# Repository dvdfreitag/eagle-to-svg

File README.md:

# eagle-to-svg    

Generates an svg image from eagle schematic and board files

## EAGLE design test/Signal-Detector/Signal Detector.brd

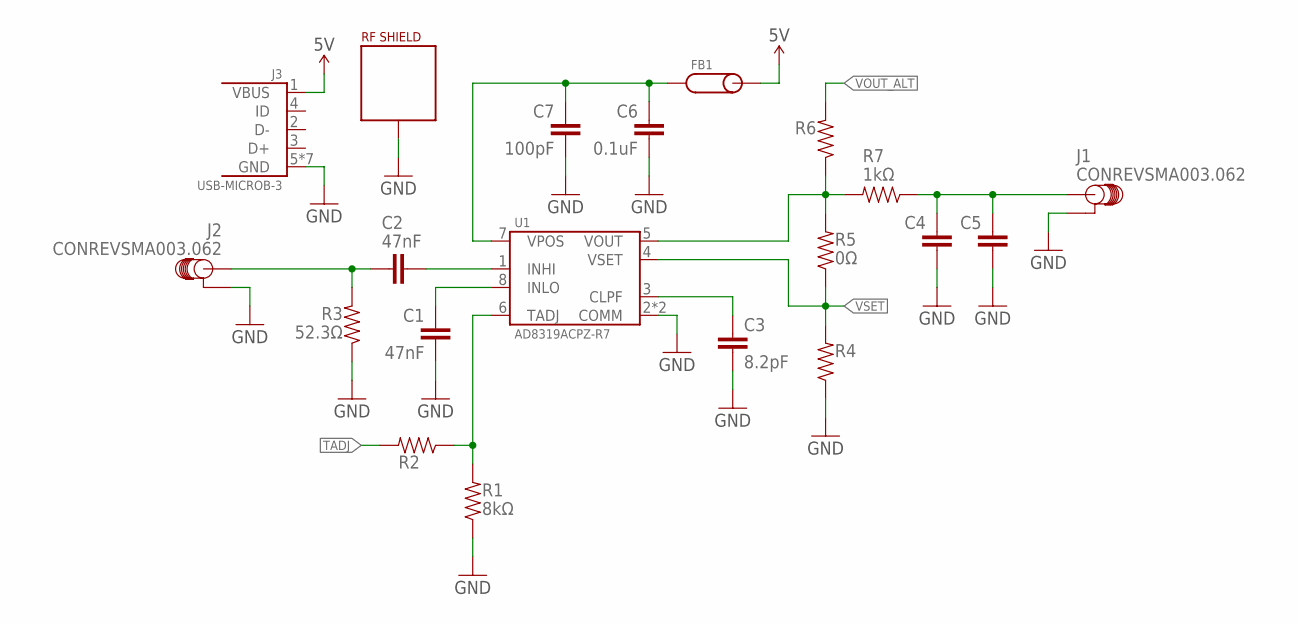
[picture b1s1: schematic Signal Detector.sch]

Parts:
C1, C2: 47nF; 0603-CAP
C3: 8.2pF; 0603-CAP
C4, C5: CAP-0603; 0603-CAP
C6: 0.1uF; 0603-CAP
C7: 100pF; 0603-CAP
FB1: FERRITE-0603; 0603-FERRITE
J1, J2: CONREVSMA003.062; SMA-EDGE
J3: USB-MICROB-3; 10118192-0001LF
R1: 8kΩ; 0603-CAP
R2, R4, R6: RESISTOR-0603; 0603-CAP
R3: 52.3Ω; 0603-CAP
R5: 0Ω; 0603-CAP
R7: 1kΩ; 0603-CAP
U1: AD8319ACPZ-R7; VFDFN-8-3X2
U$1: RF-SHIELD; RF_SHIELD-.65X.65

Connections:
5V: FB1.P$2, J3.1 (VBUS)
GND: C1.2, C3.2, C4.2, C5.2, C6.2, C7.2, J1.P$1 (GND), J1.P$2 (GND), J1.P$3 (GND), J1.P$4 (GND), J2.P$1 (GND), J2.P$2 (GND), J2.P$3 (GND), J2.P$4 (GND), J3.5 (GND), J3.P$6 (GND), J3.P$7 (GND), J3.P$8 (GND), J3.P$9 (GND), J3.P$10 (GND), J3.P$11 (GND), R1.1, R3.1, R4.1, U1.2 (COMM), U1.PAD (COMM), U$1.P$1, U$1.P$2, U$1.P$3, U$1.P$4, U$1.P$5, U$1.P$6, U$1.P$7, U$1.P$8, U$1.P$9, U$1.P$10, U$1.P$11, U$1.P$12
unnamed: R1.2, R2.1, U1.6 (TADJ)
unnamed: C1.1, U1.8 (INLO)
unnamed: C2.2, J2.SIGNAL, R3.2
unnamed: C2.1, U1.1 (INHI)
unnamed: C3.1, U1.3 (CLPF)
unnamed: R5.2, R6.1, R7.2, U1.5 (VOUT)
unnamed: C4.1, C5.1, J1.SIGNAL, R7.1
unnamed: C6.1, C7.1, FB1.P$1, U1.7 (VPOS)
TADJ: R2.2
VOUT_ALT: R6.2
VSET: R4.2, R5.1, U1.4 (VSET)

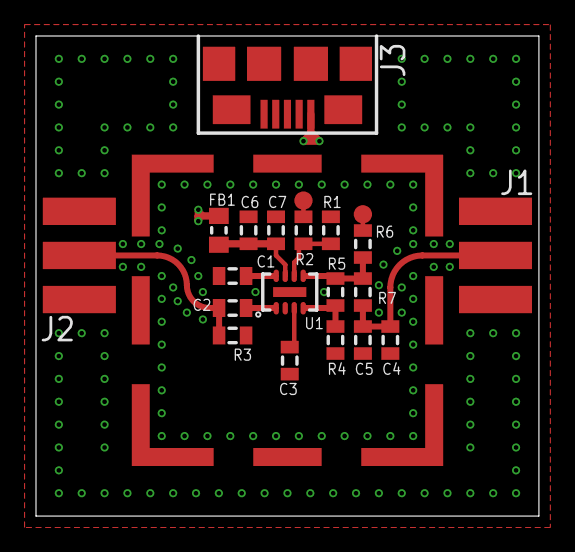
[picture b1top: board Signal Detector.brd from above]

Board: 4 copper layers, 27.9 x 26.7 mm, 20 parts (0 on the bottom side), 11 nets.

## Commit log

2016-08-22 Add license to package.json
2016-08-22 Create LICENSE
2016-08-22 Add eslint config
2016-08-22 Add some working code
    Very broken still, up to schematic layers parsed
2016-08-24 Change lint rules
    Remove some unnecessary lint rules
2016-08-24 Add test data
    Add some json files containing test data for test verification
2016-08-24 Finish parser
    Parser correctly loads layer, part instance, and symbol data from an eagle schematic
2016-08-24 Add travis config
2016-08-24 Update version
2016-08-24 Remove submodule
2016-08-24 Add board test files
